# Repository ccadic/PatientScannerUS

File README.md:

# PatientScannerUS
Ultrasound scanner to detect patients in a medical office and drive them to different areas

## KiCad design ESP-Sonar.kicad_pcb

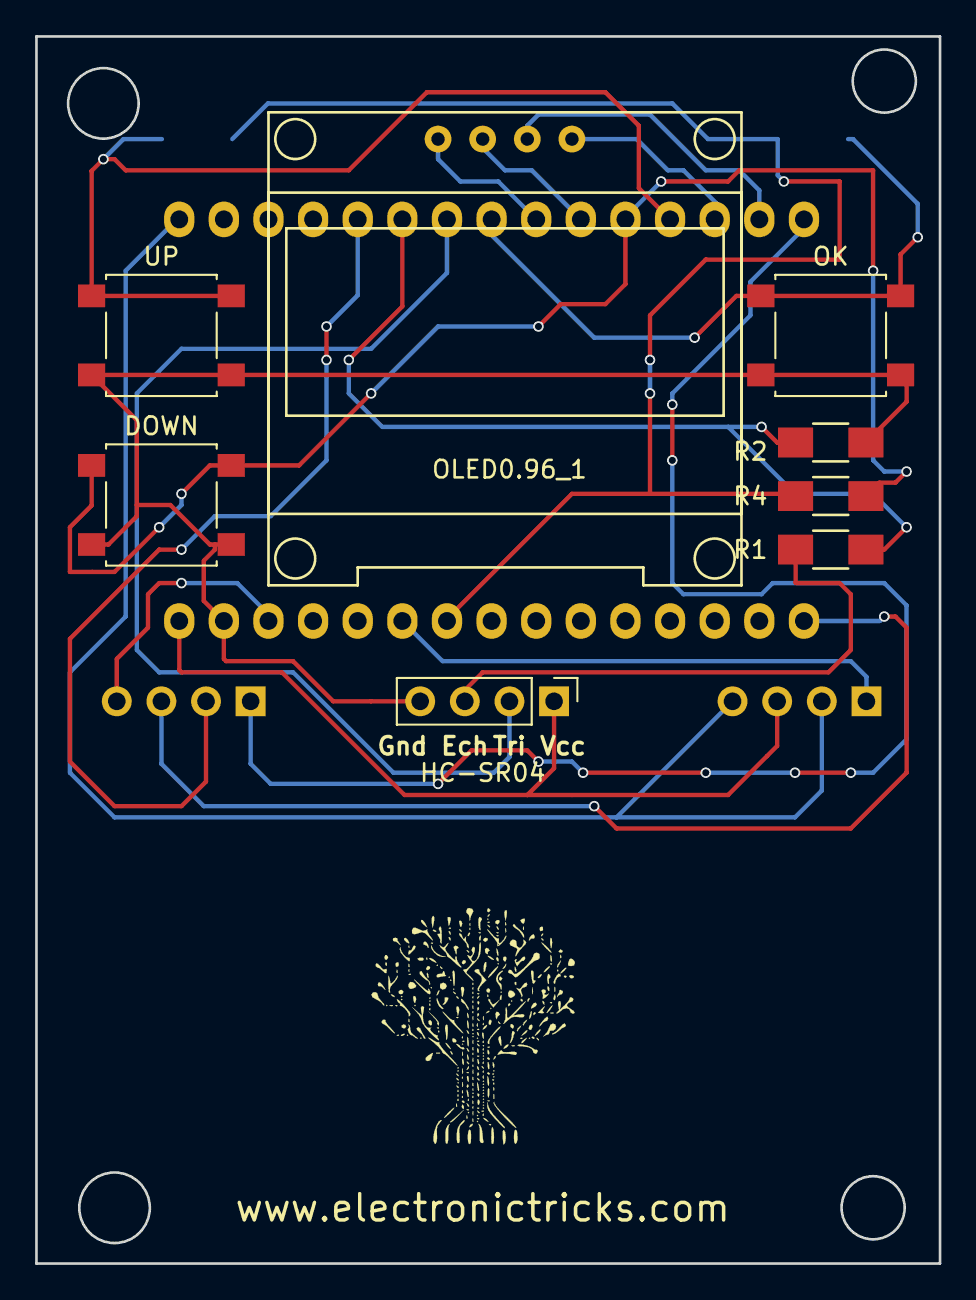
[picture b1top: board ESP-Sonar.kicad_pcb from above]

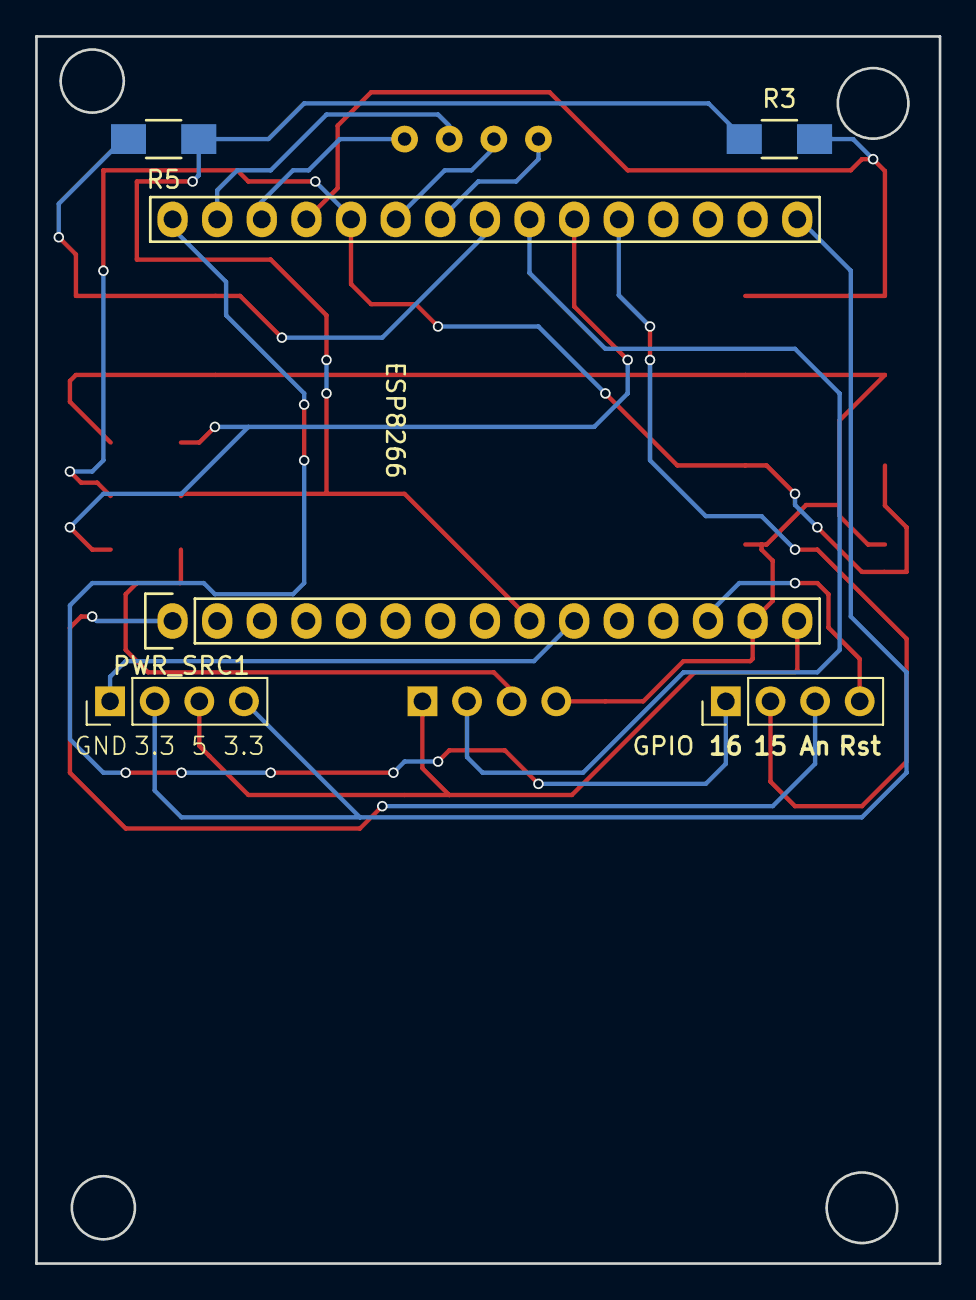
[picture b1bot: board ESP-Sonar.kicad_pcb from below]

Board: 2 copper layers, 51.4 x 69.8 mm, 13 parts (5 on the bottom side), 19 nets.

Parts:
DOWN: SW_PUSH_SMALL_H; SW_SPST_B3S-1000
ESP8266: ESP8266; NodeMCU_Amica_R2
GPIO: GPIO-Ports; Socket_Strip_Straight_1x04_Pitch2.54mm
HC-SR04: HC-SR04; Socket_Strip_Straight_1x04_Pitch2.54mm
OK: SW_PUSH_SMALL_H; SW_SPST_B3S-1000
OLED0.96_1: Oled96
PWR_SRC1: Power SRC; Socket_Strip_Straight_1x04_Pitch2.54mm
R1: 2.2k; R_1206_HandSoldering
R2, R3, R4, R5: 4.7k; R_1206_HandSoldering
UP: SW_PUSH_SMALL_H; SW_SPST_B3S-1000

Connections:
3.3v: ESP8266.9, R3.1, R4.1, R5.1
3.3v_P: ESP8266.16, PWR_SRC1.2, PWR_SRC1.4
5volts: ESP8266.15, HC-SR04.1, PWR_SRC1.3
Analog: ESP8266.1, GPIO.3
D3: ESP8266.27, R3.2, UP.1
D4: DOWN.1, ESP8266.26, R4.2
D5: ESP8266.23, OK.1, R5.2
D7: ESP8266.21, R1.2, R2.1
ECHO: HC-SR04.3, R1.1
GND: DOWN.2, ESP8266.14, HC-SR04.4, OK.2, R2.2, UP.2
GND_P: ESP8266.10, PWR_SRC1.1
GPIO15: ESP8266.20, GPIO.2
GPIO16: ESP8266.30, GPIO.1
unnamed: ESP8266.28, OLED0.96_1.1
unnamed: ESP8266.29, OLED0.96_1.2
unnamed: ESP8266.25, OLED0.96_1.3
unnamed: ESP8266.24, OLED0.96_1.4
Reset: ESP8266.13, GPIO.4
Trig: ESP8266.22, HC-SR04.2
